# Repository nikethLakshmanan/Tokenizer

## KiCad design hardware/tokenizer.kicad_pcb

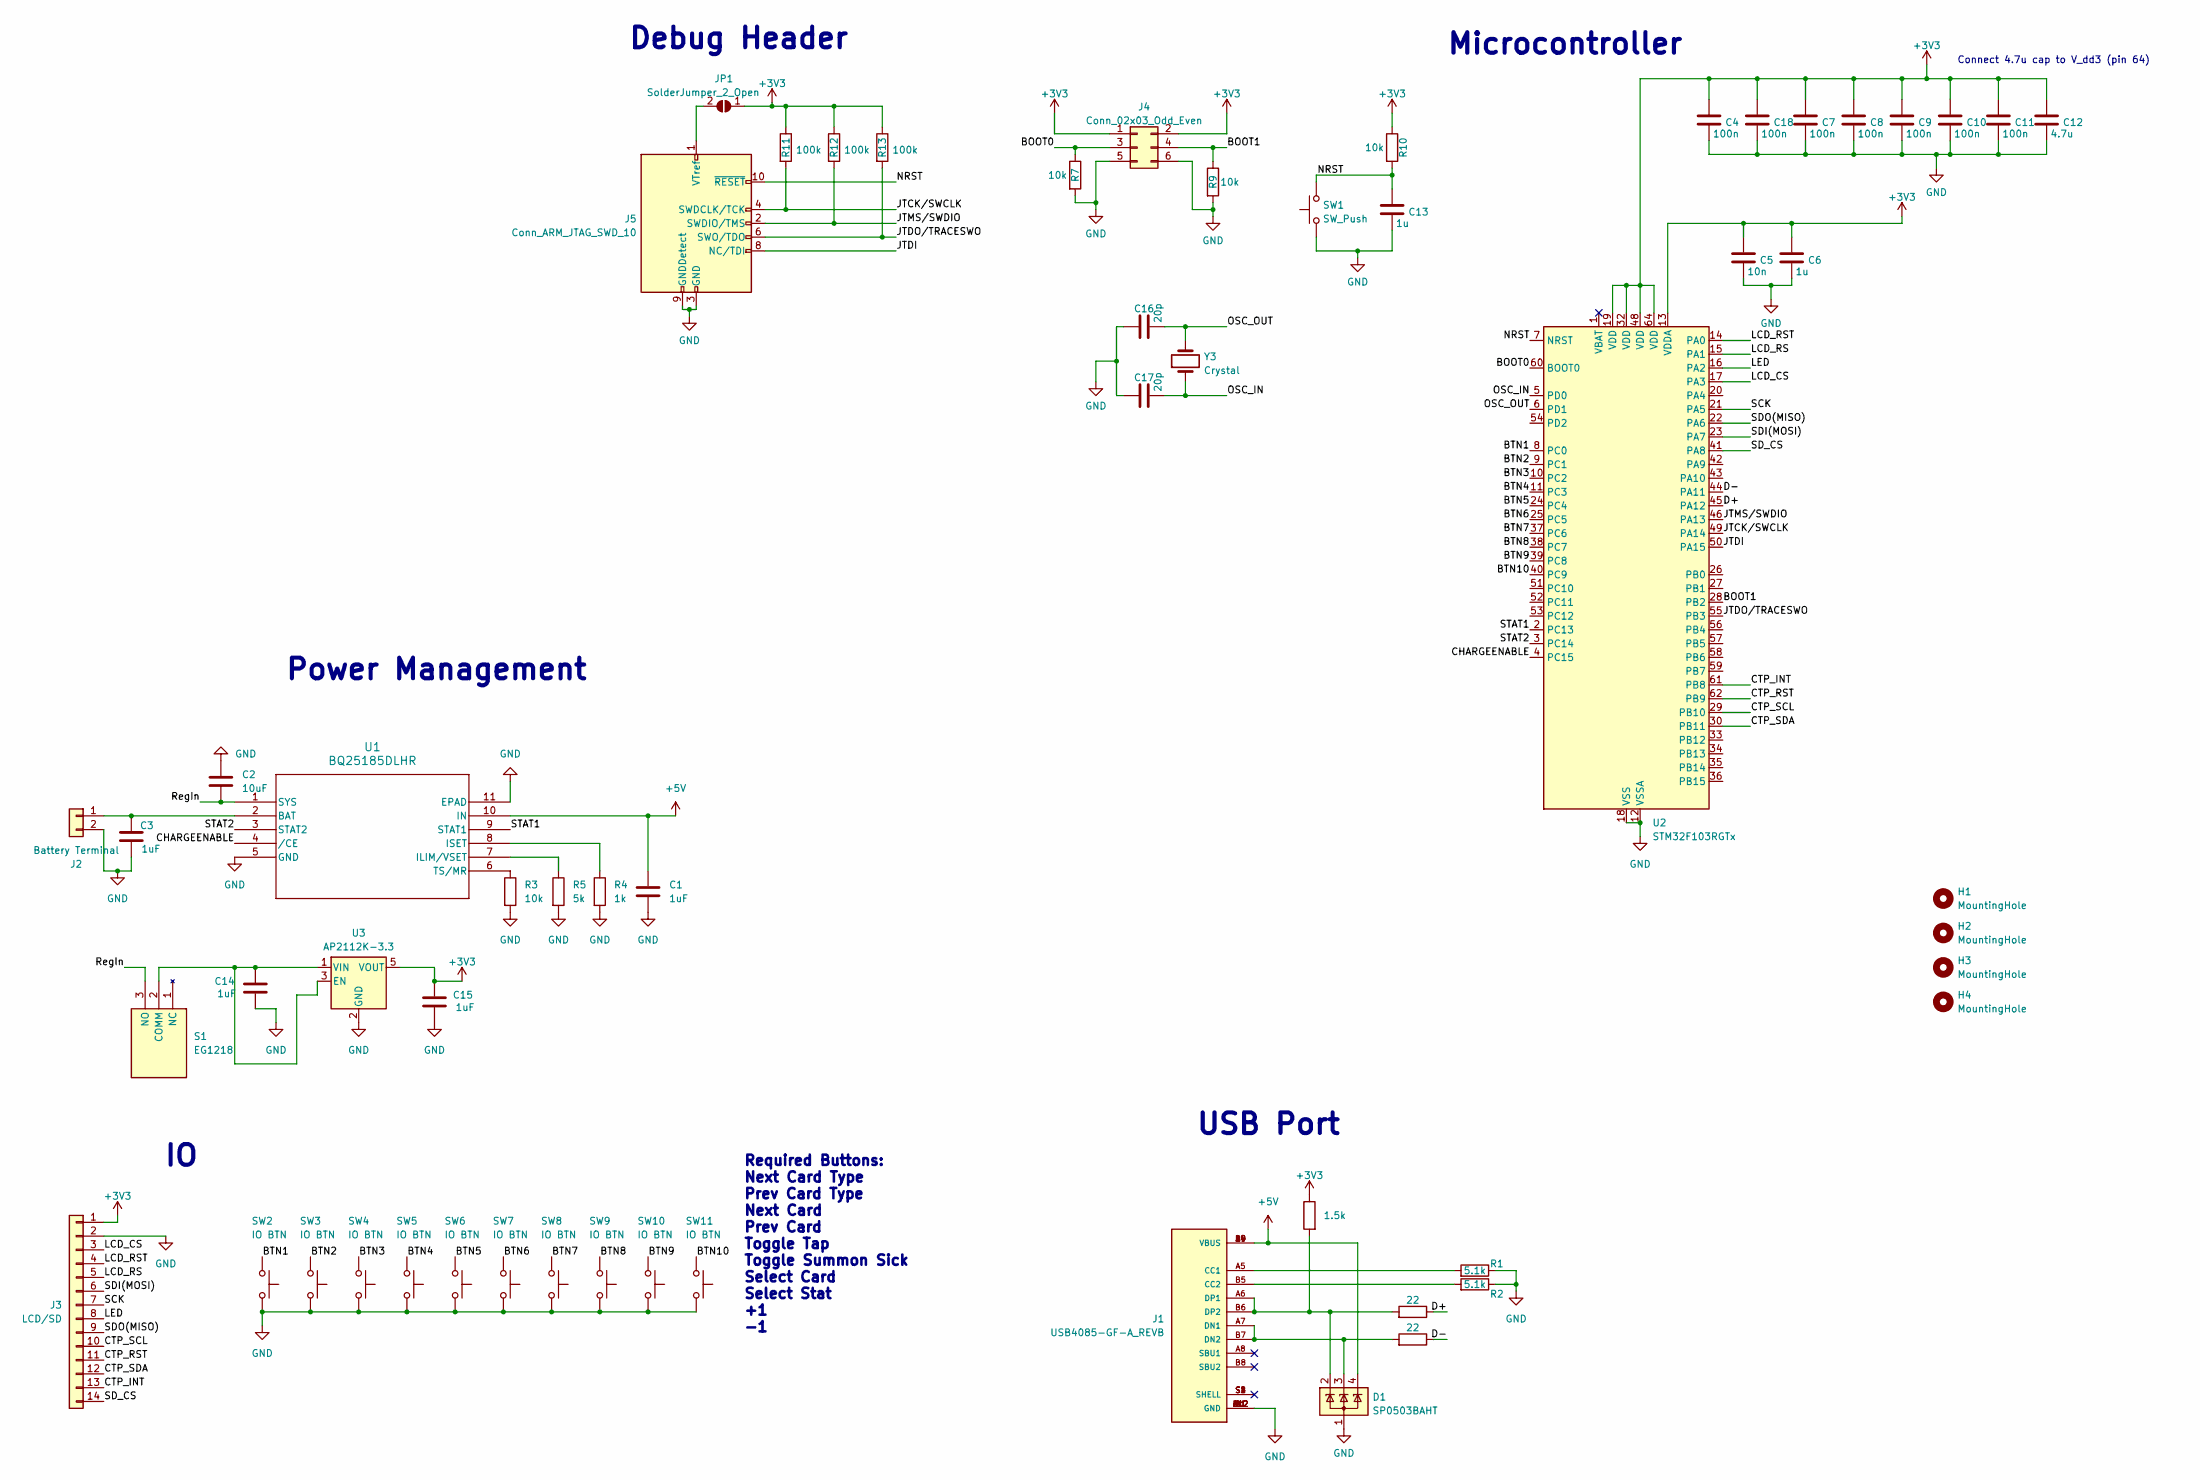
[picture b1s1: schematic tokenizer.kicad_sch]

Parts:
C1, C3, C14, C15: 1uF; C_0805_2012Metric_Pad1.18x1.45mm_HandSolder
C2: 10uF; C_0805_2012Metric_Pad1.18x1.45mm_HandSolder
C4, C7, C8, C9, C10, C11, C18: 100n; C_0603_1608Metric
C5: 10n; C_0603_1608Metric
C6, C13: 1u; C_0603_1608Metric
C12: 4.7u; C_0603_1608Metric
C16, C17: 20p; C_0603_1608Metric
D1: SP0503BAHT; SOT-143
H1, H2, H3, H4: MountingHole; MountingHole_3.2mm_M3
J1: USB4085-GF-A_REVB; GCT_USB4085-GF-A_REVB; PARTREV B
J2: Battery Terminal; JST_PH_S2B-PH-K_1x02_P2.00mm_Horizontal
J3: LCD/SD; Hirose_FH12-14S-0.5SH_1x14-1MP_P0.50mm_Horizontal
J4: Conn_02x03_Odd_Even; PinSocket_2x03_P2.54mm_Vertical
J5: Conn_ARM_JTAG_SWD_10; IDC-Header_2x05_P2.54mm_Vertical
JP1: SolderJumper_2_Open; SolderJumper-2_P1.3mm_Open_TrianglePad1.0x1.5mm
R1, R2: 5.1k; R_0805_2012Metric_Pad1.20x1.40mm_HandSolder
R3: 10k; R_0805_2012Metric_Pad1.20x1.40mm_HandSolder
R4: 1k; R_0805_2012Metric_Pad1.20x1.40mm_HandSolder
R5: 5k; R_0805_2012Metric_Pad1.20x1.40mm_HandSolder
R6, R8: 22; R_0603_1608Metric
R7, R9, R10: 10k; R_0603_1608Metric
R11, R12, R13: 100k; R_0603_1608Metric
R14: 1.5k; R_0603_1608Metric
S1: EG1218; Mouser Part Number 612-EG1218
SW1: SW_Push; SW_PUSH_6mm_H4.3mm
SW2, SW3, SW4, SW5, SW6, SW7, SW8, SW9, SW10, SW11: IO BTN; SW_PUSH_6mm_H4.3mm
U1: BQ25185DLHR; WSON10_DLH_TEX
U2: STM32F103RGTx; LQFP-64_10x10mm_P0.5mm
U3: AP2112K-3.3; SOT-23-5
Y3: Crystal; Crystal_HC49-U_Vertical

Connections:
+3V3: C4.1, C5.1, C6.1, C7.1, C8.1, C9.1, C10.1, C11.1, C12.1, C15.1, C18.1, J3.1, J4.1, J4.2, JP1.1 (A), R10.1, R11.1, R12.1, R13.1, R14.1, U2.13 (VDDA), U2.19 (VDD), U2.32 (VDD), U2.48 (VDD), U2.64 (VDD), U3.5 (VOUT)
+5V: C1.2, D1.4 (K), J1.A4 (VBUS), J1.A9 (VBUS), J1.B4 (VBUS), J1.B9 (VBUS), U1.10 (IN)
/BOOT0: J4.3, R7.1, U2.60 (BOOT0)
/BOOT1: J4.4, R9.1, U2.28 (PB2)
/BTN1: SW2.1, U2.8 (PC0)
/BTN2: SW3.1, U2.9 (PC1)
/BTN3: SW4.1, U2.10 (PC2)
/BTN4: SW5.1, U2.11 (PC3)
/BTN5: SW6.1, U2.24 (PC4)
/BTN6: SW7.1, U2.25 (PC5)
/BTN7: SW8.1, U2.37 (PC6)
/BTN8: SW9.1, U2.38 (PC7)
/BTN9: SW10.1, U2.39 (PC8)
/BTN10: SW11.1, U2.40 (PC9)
/CHARGEENABLE: U1.4 (/CE), U2.4 (PC15)
/CTP_INT: J3.13, U2.61 (PB8)
/CTP_RST: J3.11, U2.62 (PB9)
/CTP_SCL: J3.10, U2.29 (PB10)
/CTP_SDA: J3.12, U2.30 (PB11)
/D+: R6.1, U2.45 (PA12)
/D-: R8.1, U2.44 (PA11)
/JTCK/SWCLK: J5.4 (SWDCLK/TCK), R11.2, U2.49 (PA14)
/JTDI: J5.8 (NC/TDI), U2.50 (PA15)
/JTDO/TRACESWO: J5.6 (SWO/TDO), R13.2, U2.55 (PB3)
/JTMS/SWDIO: J5.2 (SWDIO/TMS), R12.2, U2.46 (PA13)
/LCD_CS: J3.3, U2.17 (PA3)
/LCD_RS: J3.5, U2.15 (PA1)
/LCD_RST: J3.4, U2.14 (PA0)
/LED: J3.8, U2.16 (PA2)
/NRST: C13.1, J5.10 (~RESET), R10.2, SW1.2, U2.7 (NRST)
/OSC_IN: C17.2, U2.5 (PD0), Y3.1
/OSC_OUT: C16.2, U2.6 (PD1), Y3.2
/RegIn: C2.1, S1.3 (NO), U1.1 (SYS)
/SCK: J3.7, U2.21 (PA5)
/SDI(MOSI): J3.6, U2.23 (PA7)
/SDO(MISO): J3.9, U2.22 (PA6)
/SD_CS: J3.14, U2.41 (PA8)
/STAT1: U1.9 (STAT1), U2.2 (PC13)
/STAT2: U1.3 (STAT2), U2.3 (PC14)
GND: C1.1, C2.2, C3.1, C4.2, C5.2, C6.2, C7.2, C8.2, C9.2, C10.2, C11.2, C12.2, C13.2, C14.2, C15.2, C16.1, C17.1, C18.2, D1.1 (A), J1.A1 (GND), J1.A12 (GND), J1.B1 (GND), J1.B12 (GND), J2.2, J3.2, J4.5, J4.6, J5.3 (GND), J5.5 (GND), J5.9 (GNDDetect), R1.1, R2.1, R3.2, R4.2, R5.2, R7.2, R9.2, SW1.1, SW2.2, SW3.2, SW4.2, SW5.2, SW6.2, SW7.2, SW8.2, SW9.2, SW10.2, SW11.2, U1.5 (GND), U1.11 (EPAD), U2.12 (VSSA), U2.18 (VSS), U2.31 (VSS), U2.47 (VSS), U2.63 (VSS), U3.2 (GND)
unnamed: J1.A5 (CC1), R1.2
unnamed: J1.B5 (CC2), R2.2
unnamed: D1.3 (K), J1.A7 (DN1), J1.B7 (DN2), R8.2
unnamed: D1.2 (K), J1.A6 (DP1), J1.B6 (DP2), R6.2, R14.2
unnamed: C3.2, J2.1, U1.2 (BAT)
unnamed: J5.1 (VTref), JP1.2 (B)
unnamed: C14.1, S1.2 (COMM), U3.1 (VIN), U3.3 (EN)
unnamed: R5.1, U1.7 (ILIM/VSET)
unnamed: R4.1, U1.8 (ISET)
unnamed: R3.1, U1.6 (TS/MR)

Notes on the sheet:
Connect 4.7u cap to V_dd3 (pin 64)
USB Port
Power Management
Required Buttons: Next Card Type Prev Card Type Next Card Prev Card Toggle Tap Toggle Summon Sick Select Card Select Stat +1 -1
Microcontroller
Debug Header

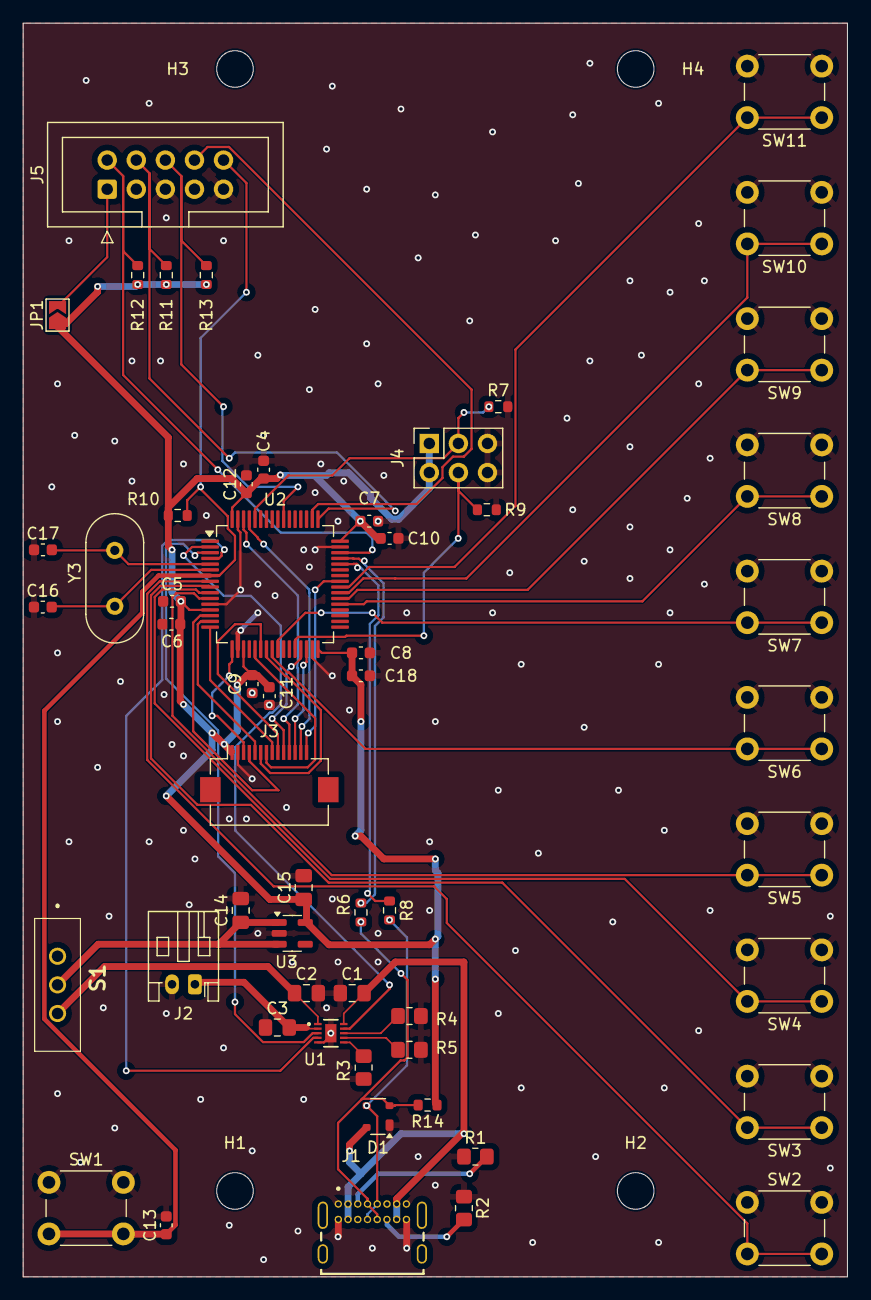
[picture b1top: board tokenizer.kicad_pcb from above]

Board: 2 copper layers, 72.0 x 109.5 mm, 59 parts (0 on the bottom side), 50 nets.

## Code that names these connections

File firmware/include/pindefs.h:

#ifndef PINDEFS_H
#define PINDEFS_H

#define TFT_CS PA_3
#define TFT_DC PA_1
#define TFT_RST PA_0
#define TFT_LED PA_2
#define SD_CS PA_8

#define BUTTON_PIN(n) PC_##n

#define STAT1 PC_13
#define STAT2 PC_14
#define CHARGE_EN PC_15

#endif

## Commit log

2024-10-08 initial setup
2024-10-09 Basic API Querying
2024-10-09 Refactoring + Card Search Tab
2024-10-09 Added RecyclerView: Allows images + text for comprehensive search
2024-10-23 UI Stuff
2024-10-23 Added Download tab, cached bit-map for images
2024-11-19 added usb funcitonality. not sure if it works
2024-11-27 tried different approach to usb
2024-11-27 USB debugging pt. 1
2024-11-27 USB debugging pt. 2
2024-11-27 should work
2024-11-27 Correct some card data, crop and scale image, basic comms
    Still needs to be turned into a BMP file, maybe use a library for that, and chunking needs to occur once it is a BMP
2024-11-28 added code for chunking and bmp conversion
2024-11-28 it works sometimes
2024-12-03 Fix bottom
2024-12-04 Stylize Home page
2024-12-11 Rename code/README.md to README.md
2024-12-11 Add firmware and hardware
2024-12-11 Notebook copy from private repo, include enclosure files
2024-12-11 update TOC
2024-12-11 TOC fix 2
